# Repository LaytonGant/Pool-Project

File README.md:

# Pool-Project
 Pool Control System for Embedded Systems

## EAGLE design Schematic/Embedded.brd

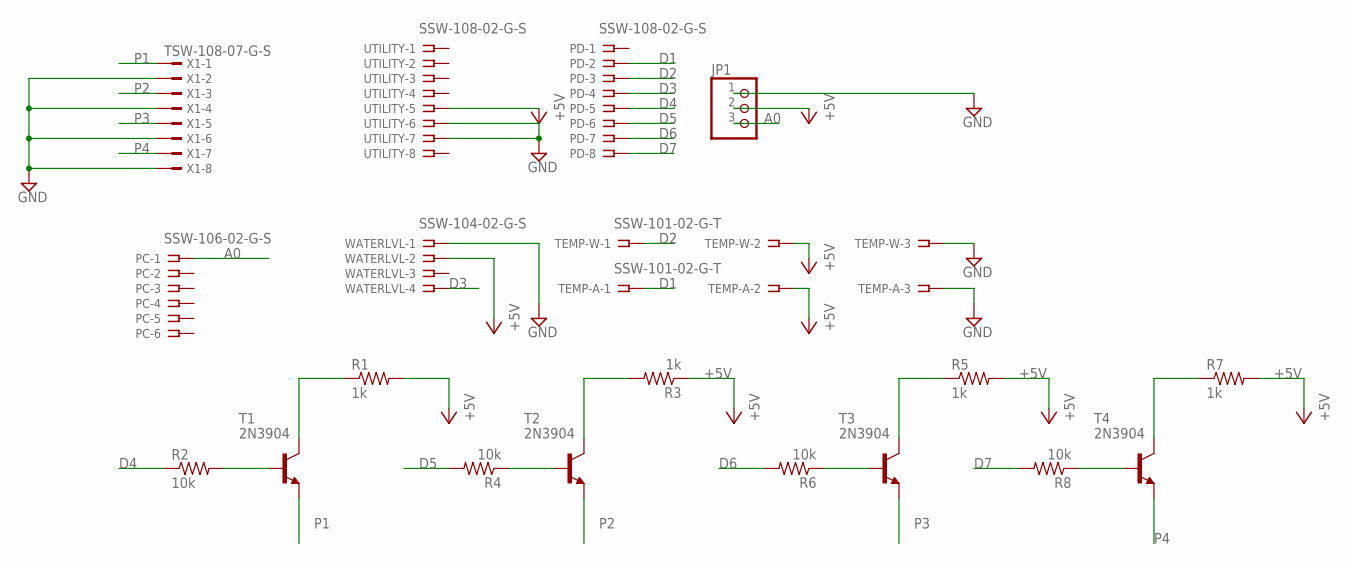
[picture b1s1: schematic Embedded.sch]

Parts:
JP1: PINHD-1X3; 1X03
PC: SSW-106-02-G-S
PD: SSW-108-02-G-S
R1, R3, R5, R7: 1k; 0411/15
R2, R4, R6, R8: 10k; 0411/15
T1, T2, T3, T4: 2N3904; TO92
TEMP-A: SSW-101-02-G-T
TEMP-W: SSW-101-02-G-T
UTILITY: SSW-108-02-G-S
WATERLVL: SSW-104-02-G-S
X1: TSW-108-07-G-S; TSW-108-XX-G-S

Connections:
+5V: JP1.2, R1.2, R3.1, R5.2, R7.2, TEMP-A.2, TEMP-W.2, UTILITY.5, WATERLVL.2
A0: JP1.3, PC.1
D1: PD.2, TEMP-A.1
D2: PD.3, TEMP-W.1
D3: PD.4, WATERLVL.4
D4: PD.5, R2.1
D5: PD.6, R4.2
D6: PD.7, R6.2
D7: PD.8, R8.2
GND: JP1.1, TEMP-A.3, TEMP-W.3, UTILITY.6, UTILITY.7, WATERLVL.1, X1.2, X1.4, X1.6, X1.8
unnamed: R2.2, T1.2 (B)
unnamed: R1.1, T1.1 (C)
unnamed: R4.1, T2.2 (B)
unnamed: R3.2, T2.1 (C)
unnamed: R6.1, T3.2 (B)
unnamed: R5.1, T3.1 (C)
unnamed: R8.1, T4.2 (B)
unnamed: R7.1, T4.1 (C)
P1: T1.3 (E), X1.1
P2: T2.3 (E), X1.3
P3: T3.3 (E), X1.5
P4: T4.3 (E), X1.7

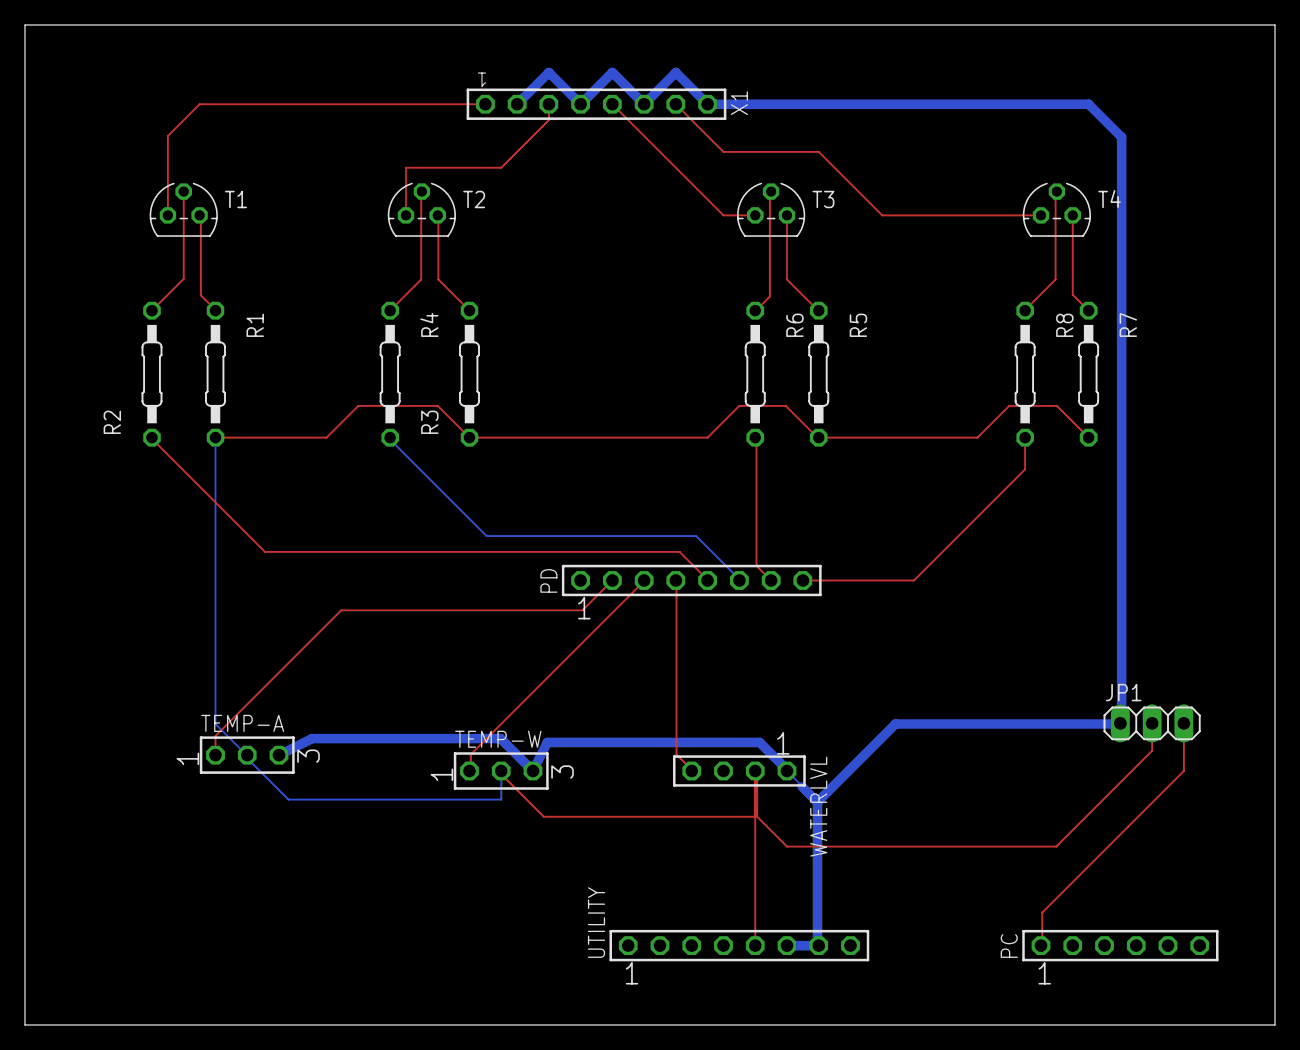
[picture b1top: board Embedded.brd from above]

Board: 2 copper layers, 100.0 x 80.0 mm, 20 parts (0 on the bottom side), 22 nets.

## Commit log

2023-02-15 Android Project File Created
2023-02-16 Website File Upload
2023-02-16 Moved into A folder
2023-02-16 Updated Files For Wesbite
2023-02-16 Updated Website
    Created buttons and stuff
2023-02-20 Submitting Data
    Submitting data via a text box and a button and redirecting you to a new page
2023-02-23 Updated Code for Website
    Updated files/folders
2023-02-23 Create DataCollectionMain.ino
    Created the arduino file for data collection
2023-02-23 Update DataCollectionMain.ino
    test
2023-02-24 Create testSuite.py
    Created Raspberry PI directory and added the test suite program for the GPIO pins.
2023-02-27 Fixed Bugs in base.html and created a button style
2023-02-27 Ds1620 Works
2023-02-27 Added Back Air Temp
    Air Temp Still Does not work, but it at least is now formatted nicer in the output.
    Water sensor was unaffected by this addition and is still fully operational.
2023-03-01 Update base.html
    Got the up and down buttons changing values for the temperature. Also go a display temp button display a numerical value
2023-03-06 Buttons
2023-03-10 Code from WebIOPi experiments
2023-03-23 Updated Arduino serial comm test code
2023-03-23 Added Pi serial comm test code
2023-03-23 Started Arduino pool communication library
2023-03-23 Tons of changes to layout
    Added bunches of buttons
2023-03-23 Added all sensors
    - Added Ph Sensor
    - Changed Air Temperature from ds1620 to same as water sensor.
    - Still Not tested in full
    - No Relay functionality has been added.
2023-03-23 Added Relay Definitions
2023-03-23 Maher.jpg
    Trying to insert a picture of Maher on the website
2023-03-23 Created test function for Arduino library.
2023-03-27 More major changes to the website
2023-03-27 Started Arduino communication library
2023-03-29 First successful test of PoolCom library
2023-03-29 I believe that I finally Finished.
2023-03-30 Fixed Disconnected 5V
2023-03-30 Maher.jpg Added
2023-03-30 Completed v1 of PoolCom library for Pi and Arduino
2023-04-03 Updated Website.py with better string formatting
2023-04-03 Updated Website Code
2023-04-05 Not needed
2023-04-06 Successful post request from checkbox
2023-04-06 Removed Semi Colin
    lol
2023-04-06 Added all checkboxes to form object
2023-04-06 Update to main website
2023-04-07 Checked Wires
    Found a GND wire that is thin to a point. Unfortunately, the PCB is already printed.
2023-04-07 Started PoolManager helper class.
2023-04-11 Updated Code
2023-04-12 Updated pool communication protocol
2023-04-12 More backend experimentation
2023-04-12 Successfully implemented form POST without refresh
2023-04-13 Made both Pool libraries static
2023-04-14 Fixed double initialization issues
2023-04-14 Added detection for relay status (doesn't work)
2023-04-14 Almost Works with serial
2023-04-19 Full restructure of a website
2023-04-19 All buttons are in
2023-04-19 Update on the Schedule to Set button
2023-04-19 Update read timeout
2023-04-19 Added PoolCom and Manager libraries
2023-04-19 Fixed syntax errors
2023-04-19 Added setStatus function
2023-04-19 Added home page data req and started temp page
2023-04-19 Started temp page backend, currently broken
2023-04-19 Update python binary
2023-04-19 Temperature Updated
2023-04-19 added comment
2023-04-20 fixed syntax
2023-04-20 More Button
2023-04-20 More changes
2023-04-20 Fixed temperature page
2023-04-20 Clock Yeee
2023-04-20 Added timer class
2023-04-20 Fixed formatting
2023-04-20 New Nice Buttons
2023-04-20 Pump it up
2023-04-20 Heater/Filter Status'
2023-04-20 Timer?
2023-04-20 Added manual device control
2023-04-20 nothing
2023-04-20 Added timer and status functionality
2023-04-20 Added int casts for redundancy
2023-04-20 timer working now :)
2023-04-20 fixed stupid int cast
2023-04-20 Nice style
2023-04-20 Sanitization
2023-04-24 Use floats instead of ints with serial comm
2023-04-24 Schedule automation testing
2023-04-24 More testing
2023-04-24 Preparing to add scheduled automation
2023-04-25 More testing with csv files
2023-04-25 Implemented file-based scheduling
2023-04-25 Fixed automation
2023-04-26 misc upload
2023-04-26 Current Struggles
2023-04-26 Fun things
2023-04-26 Schedule changes
2023-04-26 Current Code changes
2023-04-26 Made schedule adder boxes work and made auto-heater work
2023-04-26 Fixed schedule boxes and temperature automation
2023-04-26 Parsed Flask "{{events}}" into useable JS events array
2023-04-27 Fixed Layton's set button
2023-04-27 Fixed auto heater
2023-04-27 Switched int casts to float
2023-04-27 Fixed int casts to float
2023-04-27 Fixed int cast to float
